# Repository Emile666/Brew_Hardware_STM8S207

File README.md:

# Brew Automation Hardware with a STM8S207
This PCB is an evolution of what originally was an Arduino with some added hardware. The current PCB features an STM8S207R8, which comes in a 64 pins LQPF package. It has a maximum of 52 GPIO pins, contains 64K Flash, 1536 bytes EEPROM and 6 KB of RAM. Previous PCB versions were made with Eagle, starting with V4.12, KiCad is used.

<br>
*PCB Layout*

# Features
The current PCB and firmware have the following features:
- Reading of **6 x temperature sensors**: two in the HLT (one I2C LM92, one One-Wire DS18B20), one in the MLT (I2C), one in the boil-kettle (One-Wire), one at the output of the counterflow-chiller (One-Wire) and one at the MLT return-manifold (One-Wire).
- Reading of **one hardware temperature** by a LM35 temperature sensor: this is used to protect the Solid State Relays (SSR) from overheating. The LM35 is typically mounted to a heatsink of one of the SSRs that switch a heating-element.
- Reading a maximum of **4 x FS300A flowsensors**: between HLT and MLT, between MLT and boil-kettle, one at the output of the counterflow-chiller and one at the entry of the MLT return-manifold.
- Control of **8 x solenoid ball-valves** at 24 V DC.
- **2 x PWM signals (25 kHz, 28 V DC)** for the modulating gasburners (HLT and boil-kettle burners).
- Control of **4 x SSR outputs at 230 V AC**: the pump, a second pump (for the HLT counterflow-chiller), 230 V enable for the HLT gasburner and 230 V enable for the boil-kettle gasburner.
- Control of **6 x SSR outputs at 230 V AC** for the three phase heating-elements in the HLT and the boil-kettle. With this, heating of the HLT is possible with a gas-burner, with 1, 2 or 3 heating-elements of with any combination of these.
- **Synced SSR outputs** for HLT and boil-kettle, so that you only need **one three-phase connection**. The boil-kettle outputs have priority over the HLT outputs, meaning that if (on any phase of 230 V) both HLT and boil-kettle are heating, only the boil-kettle is activated.
  It is also possible to use just one (or two) of the three-phases, depending on the number of heating-elements inside the HLT and/or boil-kettle. The firmware is capable of addressing one, two or three heating-elements per kettle.
- **Ethernet and USB connection** to PC: USB-connection is used for debugging, main connection between PC-program and the firmware is Ethernet.
- **Frontpanel LEDs (24 in total)** that show the status of all actuators. They are controlled by a MAX7219 LED Display Driver, located on a separate PCB, the frontpanel PCB.

# Schematics (.pdf)
[Brew Hardware schematics](./brew_HW_stm8s207_r430.pdf)<br>
*Brew Hardware Schematics*

# Interactive Bill-of-Materials (BOM)
[Brew Hardware BOM](http://htmlpreview.github.io/?https://github.com/Emile666/Brew_Hardware_STM8S207/blob/main/bom/ibom.html)<br>
*Brew Hardware BOM*

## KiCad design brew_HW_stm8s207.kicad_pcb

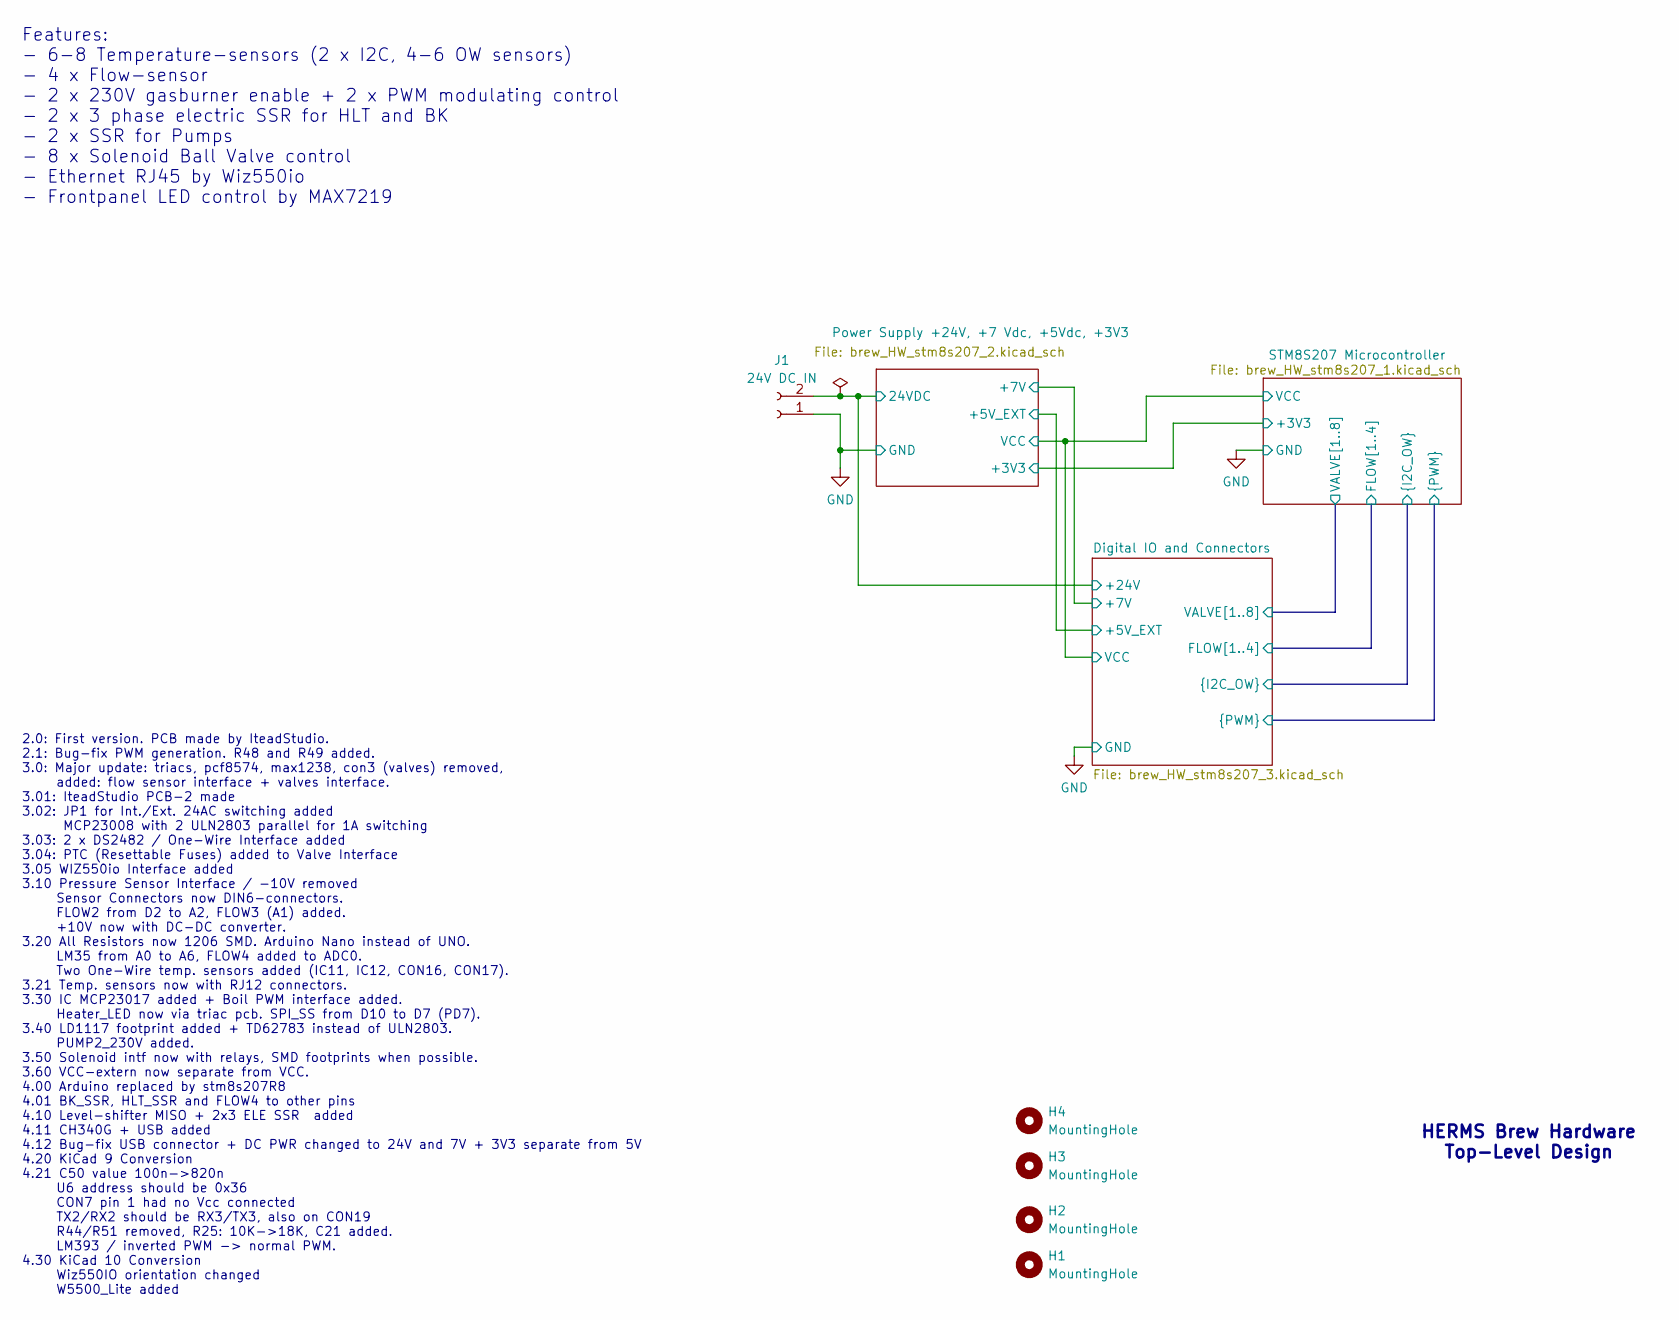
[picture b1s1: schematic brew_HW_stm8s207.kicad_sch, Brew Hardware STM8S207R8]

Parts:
H1, H2, H3, H4: MountingHole; MountingHole_3.2mm_M3
J1: 24V DC IN; AK500_2

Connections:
/Digital IO and Connectors/+24V: J1.2; also elsewhere on the board
GND: J1.1; also elsewhere on the board

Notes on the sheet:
Features: - 6-8 Temperature-sensors (2 x I2C, 4-6 OW sensors) - 4 x Flow-sensor - 2 x 230V gasburner enable + 2 x PWM modulating control - 2 x 3 phase electric SSR for HLT and BK - 2 x SSR for Pumps - 8 x Solenoid Ball Valve control - Ethernet RJ45 by Wiz550io - Frontpanel LED control by MAX7219
2.0: First version. PCB made by IteadStudio. 2.1: Bug-fix PWM generation. R48 and R49 added. 3.0: Major update: triacs, pcf8574, max1238, con3 (valves) removed, added: flow sensor interface + valves interface. 3.01: IteadStudio PCB-2 made 3.02: JP1 for Int./Ext. 24AC switching added MCP23008 with 2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
HERMS Brew Hardware Top-Level Design

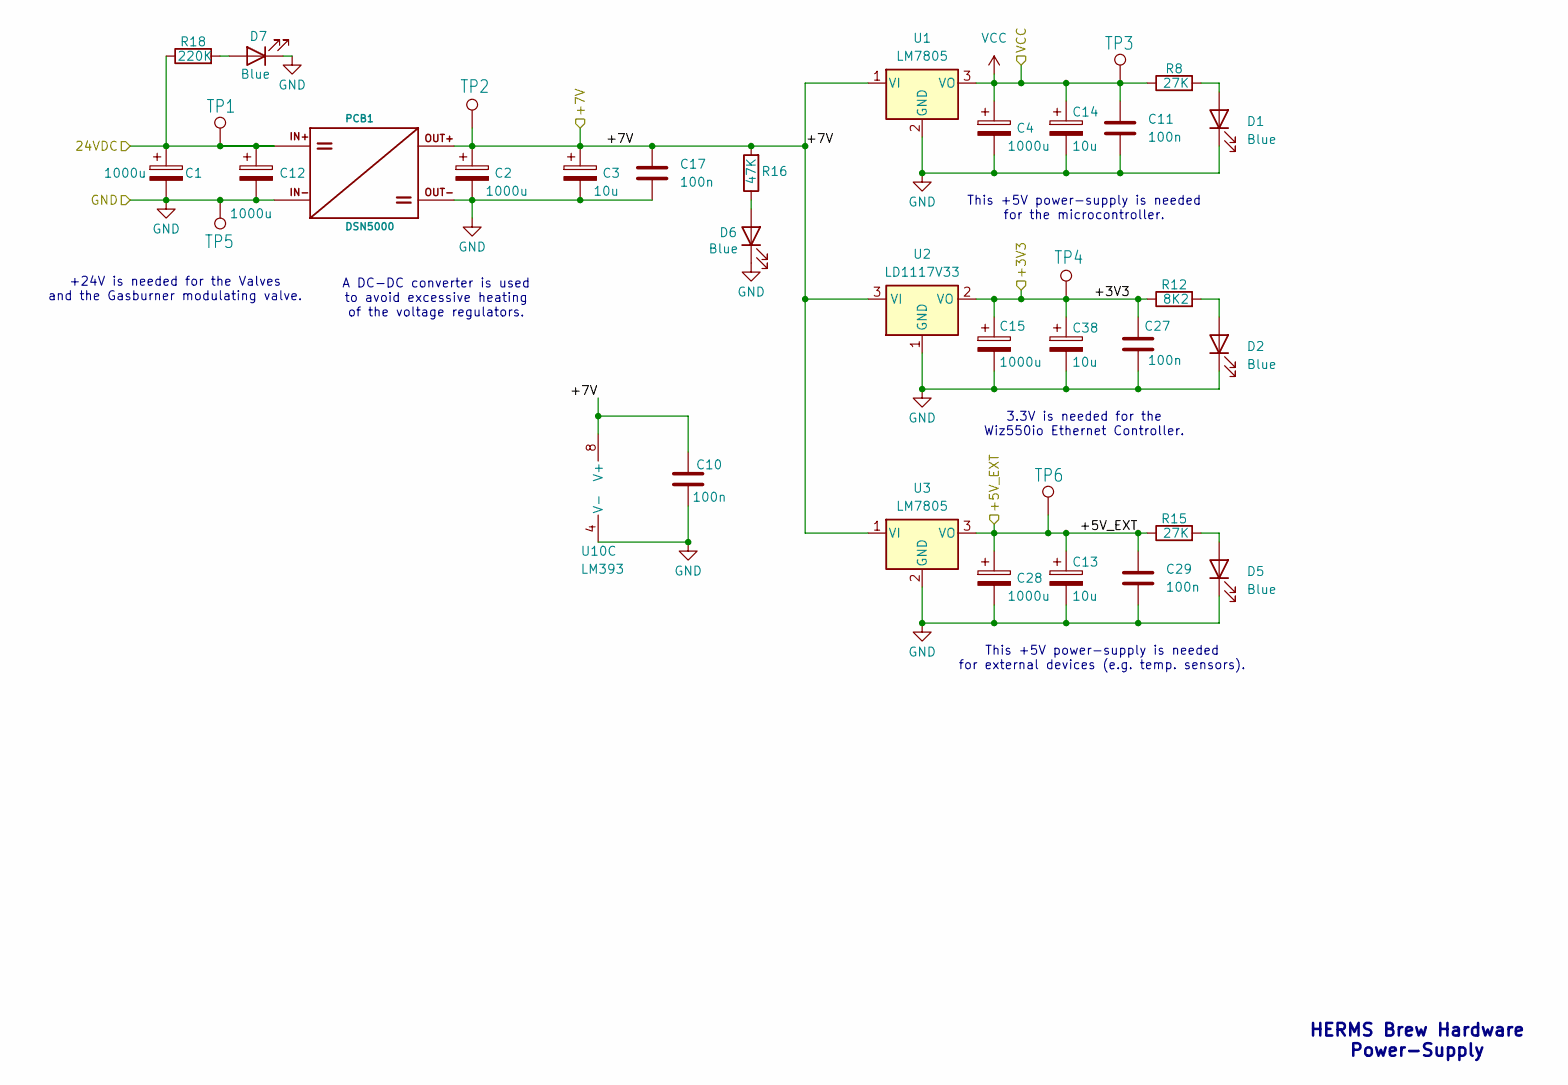
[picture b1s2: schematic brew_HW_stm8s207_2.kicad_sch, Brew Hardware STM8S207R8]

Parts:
C1, C2, C4, C12, C15, C28: 1000u; CP_Radial_D12.5mm_P5.00mm
C3, C13, C14, C38: 10u; CP_Radial_D5.0mm_P2.00mm
C10, C11, C17, C27, C29: 100n; C_1206_3216Metric
D1, D2, D5, D6, D7: Blue; LED_1206_3216Metric
PCB1: DSN5000; DSN5000_DCDC_CONVERTER
R8, R15: 27K; R_1206_3216Metric
R12: 8K2; R_1206_3216Metric
R16: 47K; R_1206_3216Metric
R18: 220K; R_1206_3216Metric
TP1: +24V; TestPoint_Loop_D2.54mm_Drill1.5mm_Beaded
TP2: +7V; TestPoint_Loop_D2.54mm_Drill1.5mm_Beaded
TP3: VCC; TestPoint_Loop_D2.54mm_Drill1.5mm_Beaded
TP4: +3V3; TestPoint_Loop_D2.54mm_Drill1.5mm_Beaded
TP5: GND; TestPoint_Loop_D2.54mm_Drill1.5mm_Beaded
TP6: +5VE; TestPoint_Loop_D2.54mm_Drill1.5mm_Beaded
U1, U3: LM7805; TO-220-3_Vertical
U2: LD1117V33; TO-220-3_Vertical
U10: LM393; DIP-8_W7.62mm

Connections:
/Digital IO and Connectors/+5V_EXT: C13.1, C28.1, C29.1, R15.1, TP6.1 (1_1), U3.3 (VO); also elsewhere on the board
/Digital IO and Connectors/+7V: C2.1, C3.1, C10.1, C17.1, PCB1.P$3, R16.2, TP2.1 (1_1), U1.1 (VI), U2.3 (VI), U3.1 (VI), U10.8 (V+); also elsewhere on the board
/Digital IO and Connectors/+24V: C1.1, C12.1, PCB1.PX$1 (IN+), R18.1, TP1.1 (1_1); also elsewhere on the board
/Power Supply +24V, +7 Vdc, +5Vdc, +3V3/+3V3: C15.1, C27.1, C38.1, R12.1, TP4.1 (1_1), U2.2 (VO); also elsewhere on the board
GND: C1.2, C2.2, C3.2, C4.2, C10.2, C11.2, C12.2, C13.2, C14.2, C15.2, C17.2, C27.2, C28.2, C29.2, C38.2, D1.1 (K), D2.1 (K), D5.1 (K), D6.1 (K), D7.1 (K), PCB1.P$2, PCB1.P$4, TP5.1 (1_1), U1.2 (GND), U2.1 (GND), U3.2 (GND), U10.4 (V-); also elsewhere on the board
unnamed: D1.2 (A), R8.2
unnamed: D2.2 (A), R12.2
unnamed: D5.2 (A), R15.2
unnamed: D6.2 (A), R16.1
unnamed: D7.2 (A), R18.2
VCC: C4.1, C11.1, C14.1, R8.1, TP3.1 (1_1), U1.3 (VO); also elsewhere on the board

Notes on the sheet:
This +5V power-supply is needed for external devices (e.g. temp. sensors).
+24V is needed for the Valves and the Gasburner modulating valve.
HERMS Brew Hardware Power-Supply
This +5V power-supply is needed for the microcontroller.
A DC-DC converter is used to avoid excessive heating of the voltage regulators.
3.3V is needed for the Wiz550io Ethernet Controller.

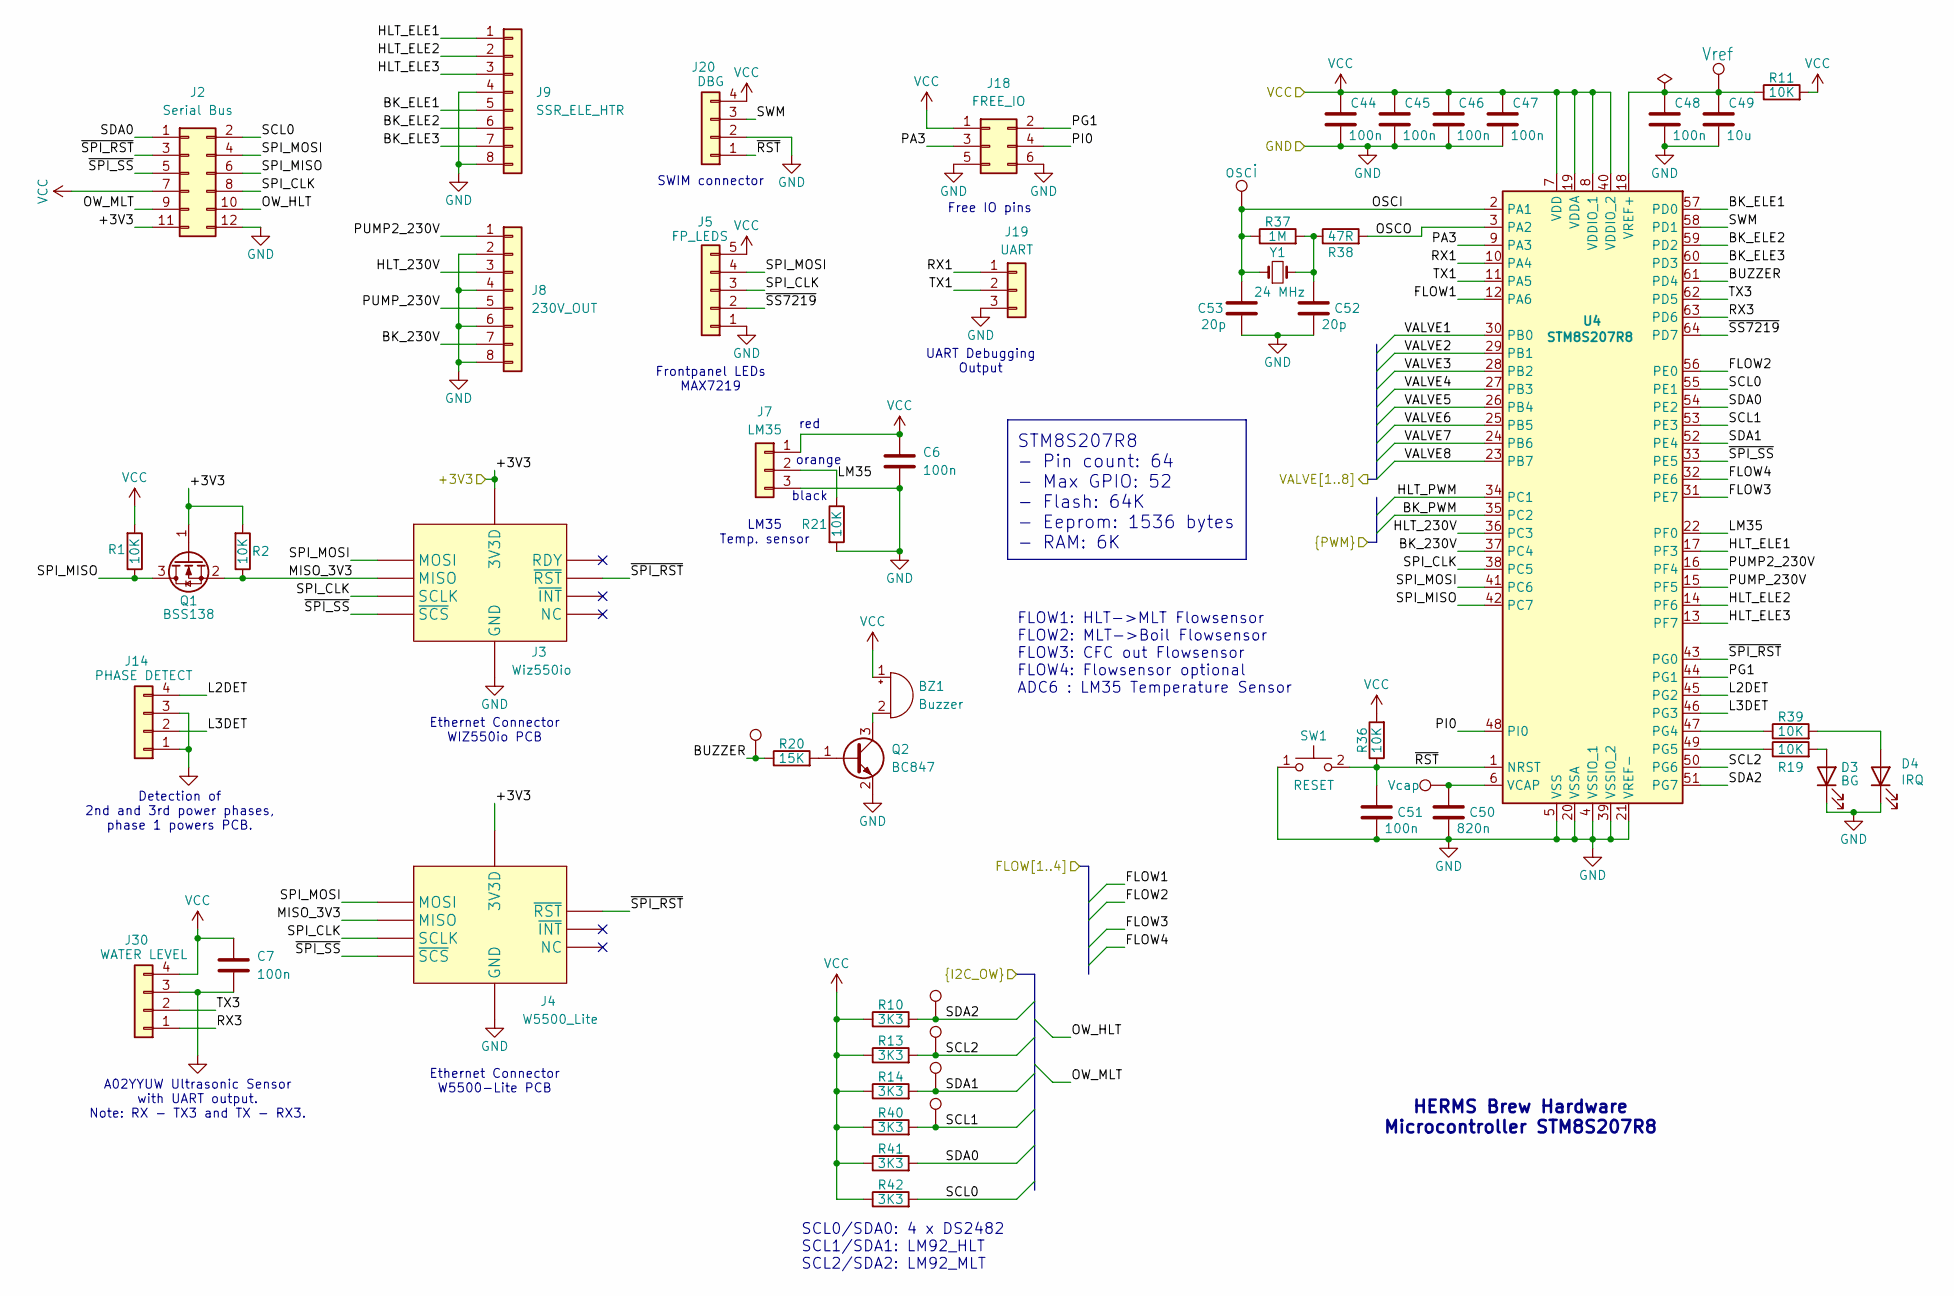
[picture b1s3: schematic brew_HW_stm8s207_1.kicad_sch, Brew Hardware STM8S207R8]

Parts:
BZ1: Buzzer; Buzzer_12x9.5RM7.6
C6, C7, C44, C45, C46, C47, C48, C51: 100n; C_1206_3216Metric
C49: 10u; CP_Radial_D5.0mm_P2.00mm
C50: 820n; C_1206_3216Metric
C52, C53: 20p; C_1206_3216Metric
D3: BG; LED_1206_3216Metric
D4: IRQ; LED_1206_3216Metric
J2: Serial Bus; PinSocket_2x06_P2.54mm_Vertical
J3: Wiz550io; WIZ550IO
J4: W5500_Lite; W55000_Lite
J5: FP_LEDS; PinSocket_1x05_P2.54mm_Vertical
J7: LM35; PinSocket_1x03_P2.54mm_Vertical
J8: 230V_OUT; PinHeader_1x08_P2.54mm_Vertical
J9: SSR_ELE_HTR; PinHeader_1x08_P2.54mm_Vertical
J14: PHASE DETECT; PinSocket_1x04_P2.54mm_Vertical
J18: FREE_IO; PinSocket_2x03_P2.54mm_Vertical
J19: UART; PinSocket_1x03_P2.54mm_Vertical
J20: DBG; PinSocket_1x04_P2.54mm_Vertical
J30: WATER LEVEL; PinSocket_1x04_P2.54mm_Vertical
Q1: BSS138; SOT-23
Q2: BC847; SOT-23
R1, R2, R11, R19, R21, R36, R39: 10K; R_1206_3216Metric
R10, R13, R14, R40, R41, R42: 3K3; R_1206_3216Metric
R20: 15K; R_1206_3216Metric
R37: 1M; R_1206_3216Metric
R38: 47R; R_1206_3216Metric
SW1: RESET; SW_Tactile_Straight_KSA0Axx1LFTR
TP7: Vref; TestPoint_Pad_D1.0mm
TP8: Vcap; TestPoint_Pad_D1.0mm
TP9: sda2; TestPoint_Pad_D1.0mm
TP10: scl2; TestPoint_Pad_D1.0mm
TP11: sda1; TestPoint_Pad_D1.0mm
TP12: scl1; TestPoint_Pad_D1.0mm
TP13: bz; TestPoint_Pad_D1.0mm
TP14: osci; TestPoint_Pad_D1.0mm
U4: STM8S207R8; LQFP-64_10x10mm_P0.5mm
Y1: 24 MHz; Crystal_HC49-4H_Vertical

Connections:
/Digital IO and Connectors/BK_PWM: U4.35 (PC2); also elsewhere on the board
/Digital IO and Connectors/FLOW1: U4.12 (PA6); also elsewhere on the board
/Digital IO and Connectors/FLOW2: U4.56 (PE0); also elsewhere on the board
/Digital IO and Connectors/FLOW3: U4.31 (PE7); also elsewhere on the board
/Digital IO and Connectors/FLOW4: U4.32 (PE6); also elsewhere on the board
/Digital IO and Connectors/HLT_PWM: U4.34 (PC1); also elsewhere on the board
/Digital IO and Connectors/OW_HLT: J2.10; also elsewhere on the board
/Digital IO and Connectors/OW_MLT: J2.9; also elsewhere on the board
/Digital IO and Connectors/SCL0: J2.2, R42.2, U4.55 (PE1); also elsewhere on the board
/Digital IO and Connectors/SCL1: R40.2, TP12.1 (1_1), U4.53 (PE3); also elsewhere on the board
/Digital IO and Connectors/SCL2: R13.2, TP10.1 (1_1), U4.50 (PG6); also elsewhere on the board
/Digital IO and Connectors/SDA0: J2.1, R41.2, U4.54 (PE2); also elsewhere on the board
/Digital IO and Connectors/SDA1: R14.2, TP11.1 (1_1), U4.52 (PE4); also elsewhere on the board
/Digital IO and Connectors/SDA2: R10.2, TP9.1 (1_1), U4.51 (PG7); also elsewhere on the board
/Digital IO and Connectors/VALVE1: U4.30 (PB0); also elsewhere on the board
/Digital IO and Connectors/VALVE2: U4.29 (PB1); also elsewhere on the board
/Digital IO and Connectors/VALVE3: U4.28 (PB2); also elsewhere on the board
/Digital IO and Connectors/VALVE4: U4.27 (PB3); also elsewhere on the board
/Digital IO and Connectors/VALVE5: U4.26 (PB4); also elsewhere on the board
/Digital IO and Connectors/VALVE6: U4.25 (PB5); also elsewhere on the board
/Digital IO and Connectors/VALVE7: U4.24 (PB6); also elsewhere on the board
/Digital IO and Connectors/VALVE8: U4.23 (PB7); also elsewhere on the board
/Power Supply +24V, +7 Vdc, +5Vdc, +3V3/+3V3: J2.11, J3.6 (3V3D), J4.6 (3V3D), Q1.1 (G), R2.2; also elsewhere on the board
/STM8S207 Microcontroller/BK_230V: J8.7, U4.37 (PC4)
/STM8S207 Microcontroller/BK_ELE1: J9.5, U4.57 (PD0)
/STM8S207 Microcontroller/BK_ELE2: J9.6, U4.59 (PD2)
/STM8S207 Microcontroller/BK_ELE3: J9.7, U4.60 (PD3)
/STM8S207 Microcontroller/BUZZER: R20.1, TP13.1 (1_1), U4.61 (PD4)
/STM8S207 Microcontroller/HLT_230V: J8.3, U4.36 (PC3)
/STM8S207 Microcontroller/HLT_ELE1: J9.1, U4.17 (PF3)
/STM8S207 Microcontroller/HLT_ELE2: J9.2, U4.14 (PF6)
/STM8S207 Microcontroller/HLT_ELE3: J9.3, U4.13 (PF7)
/STM8S207 Microcontroller/L2DET: J14.4, U4.45 (PG2)
/STM8S207 Microcontroller/L3DET: J14.2, U4.46 (PG3)
/STM8S207 Microcontroller/LM35: J7.2, R21.1, U4.22 (PF0)
/STM8S207 Microcontroller/MISO_3V3: J3.3 (MISO), J4.3 (MISO), Q1.2 (S), R2.1
/STM8S207 Microcontroller/OSCI: C53.1, R37.1, TP14.1 (1_1), U4.2 (PA1), Y1.1
/STM8S207 Microcontroller/OSCO: R38.2, U4.3 (PA2)
/STM8S207 Microcontroller/PA3: J18.3, U4.9 (PA3)
/STM8S207 Microcontroller/PG1: J18.2, U4.44 (PG1)
/STM8S207 Microcontroller/PI0: J18.4, U4.48 (PI0)
/STM8S207 Microcontroller/PUMP2_230V: J8.1, U4.16 (PF4)
/STM8S207 Microcontroller/PUMP_230V: J8.5, U4.15 (PF5)
/STM8S207 Microcontroller/RX1: J19.1, U4.10 (PA4)
/STM8S207 Microcontroller/RX3: J30.1, U4.63 (PD6)
/STM8S207 Microcontroller/SPI_CLK: J2.8, J3.4 (SCLK), J4.4 (SCLK), J5.3, U4.38 (PC5)
/STM8S207 Microcontroller/SPI_MISO: J2.6, Q1.3 (D), R1.1, U4.42 (PC7)
/STM8S207 Microcontroller/SPI_MOSI: J2.4, J3.2 (MOSI), J4.2 (MOSI), J5.4, U4.41 (PC6)
/STM8S207 Microcontroller/SWM: J20.3, U4.58 (PD1)
/STM8S207 Microcontroller/TX1: J19.2, U4.11 (PA5)
/STM8S207 Microcontroller/TX3: J30.2, U4.62 (PD5)
/STM8S207 Microcontroller/~RST: C51.1, J20.1, R36.1, SW1.2, U4.1 (NRST)
/STM8S207 Microcontroller/~SPI_RST: J2.3, J3.9 (~RST), J4.9 (~RST), U4.43 (PG0)
/STM8S207 Microcontroller/~SPI_SS: J2.5, J3.5 (~SCS), J4.5 (~SCS), U4.33 (PE5)
/STM8S207 Microcontroller/~SS7219: J5.2, U4.64 (PD7)
GND: C6.2, C7.2, C44.2, C45.2, C46.2, C47.2, C48.2, C49.2, C50.2, C51.2, C52.2, C53.2, D3.1 (K), D4.1 (K), J2.12, J3.1 (GND), J4.1 (GND), J5.1, J7.3, J8.2, J8.4, J8.6, J8.8, J9.4, J9.8, J14.1, J14.3, J18.5, J18.6, J19.3, J20.2, J30.3, Q2.2 (E), R21.2, SW1.1, U4.4 (VSSIO_1), U4.5 (VSS), U4.20 (VSSA), U4.21 (VREF-), U4.39 (VSSIO_2); also elsewhere on the board
unnamed: BZ1.2 (-), Q2.3 (C)
unnamed: C52.1, R37.2, R38.1, Y1.2
unnamed: D3.2 (A), R19.2
unnamed: D4.2 (A), R39.2
unnamed: Q2.1 (B), R20.2
unnamed: R39.1, U4.47 (PG4)
unnamed: R19.1, U4.49 (PG5)
unnamed: C50.1, TP8.1 (1_1), U4.6 (VCAP)
unnamed: C48.1, C49.1, R11.1, TP7.1 (1_1), U4.18 (VREF+)
VCC: BZ1.1 (+), C6.1, C7.1, C44.1, C45.1, C46.1, C47.1, J2.7, J5.5, J7.1, J18.1, J20.4, J30.4, R1.2, R10.1, R11.2, R13.1, R14.1, R36.2, R40.1, R41.1, R42.1, U4.7 (VDD), U4.8 (VDDIO_1), U4.19 (VDDA), U4.40 (VDDIO_2); also elsewhere on the board

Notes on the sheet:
SWIM connector
Ethernet Connector WIZ550io PCB
SCL0/SDA0: 4 x DS2482 SCL1/SDA1: LM92_HLT SCL2/SDA2: LM92_MLT
black
FLOW1: HLT->MLT Flowsensor FLOW2: MLT->Boil Flowsensor FLOW3: CFC out Flowsensor FLOW4: Flowsensor optional ADC6 : LM35 Temperature Sensor
LM35 Temp. sensor
Frontpanel LEDs MAX7219
Ethernet Connector W5500-Lite PCB
orange
HERMS Brew Hardware Microcontroller STM8S207R8
STM8S207R8 - Pin count: 64 - Max GPIO: 52 - Flash: 64K - Eeprom: 1536 bytes - RAM: 6K
UART Debugging Output
A02YYUW Ultrasonic Sensor with UART output. Note: RX - TX3 and TX - RX3.
Detection of 2nd and 3rd power phases, phase 1 powers PCB.
Free IO pins
red

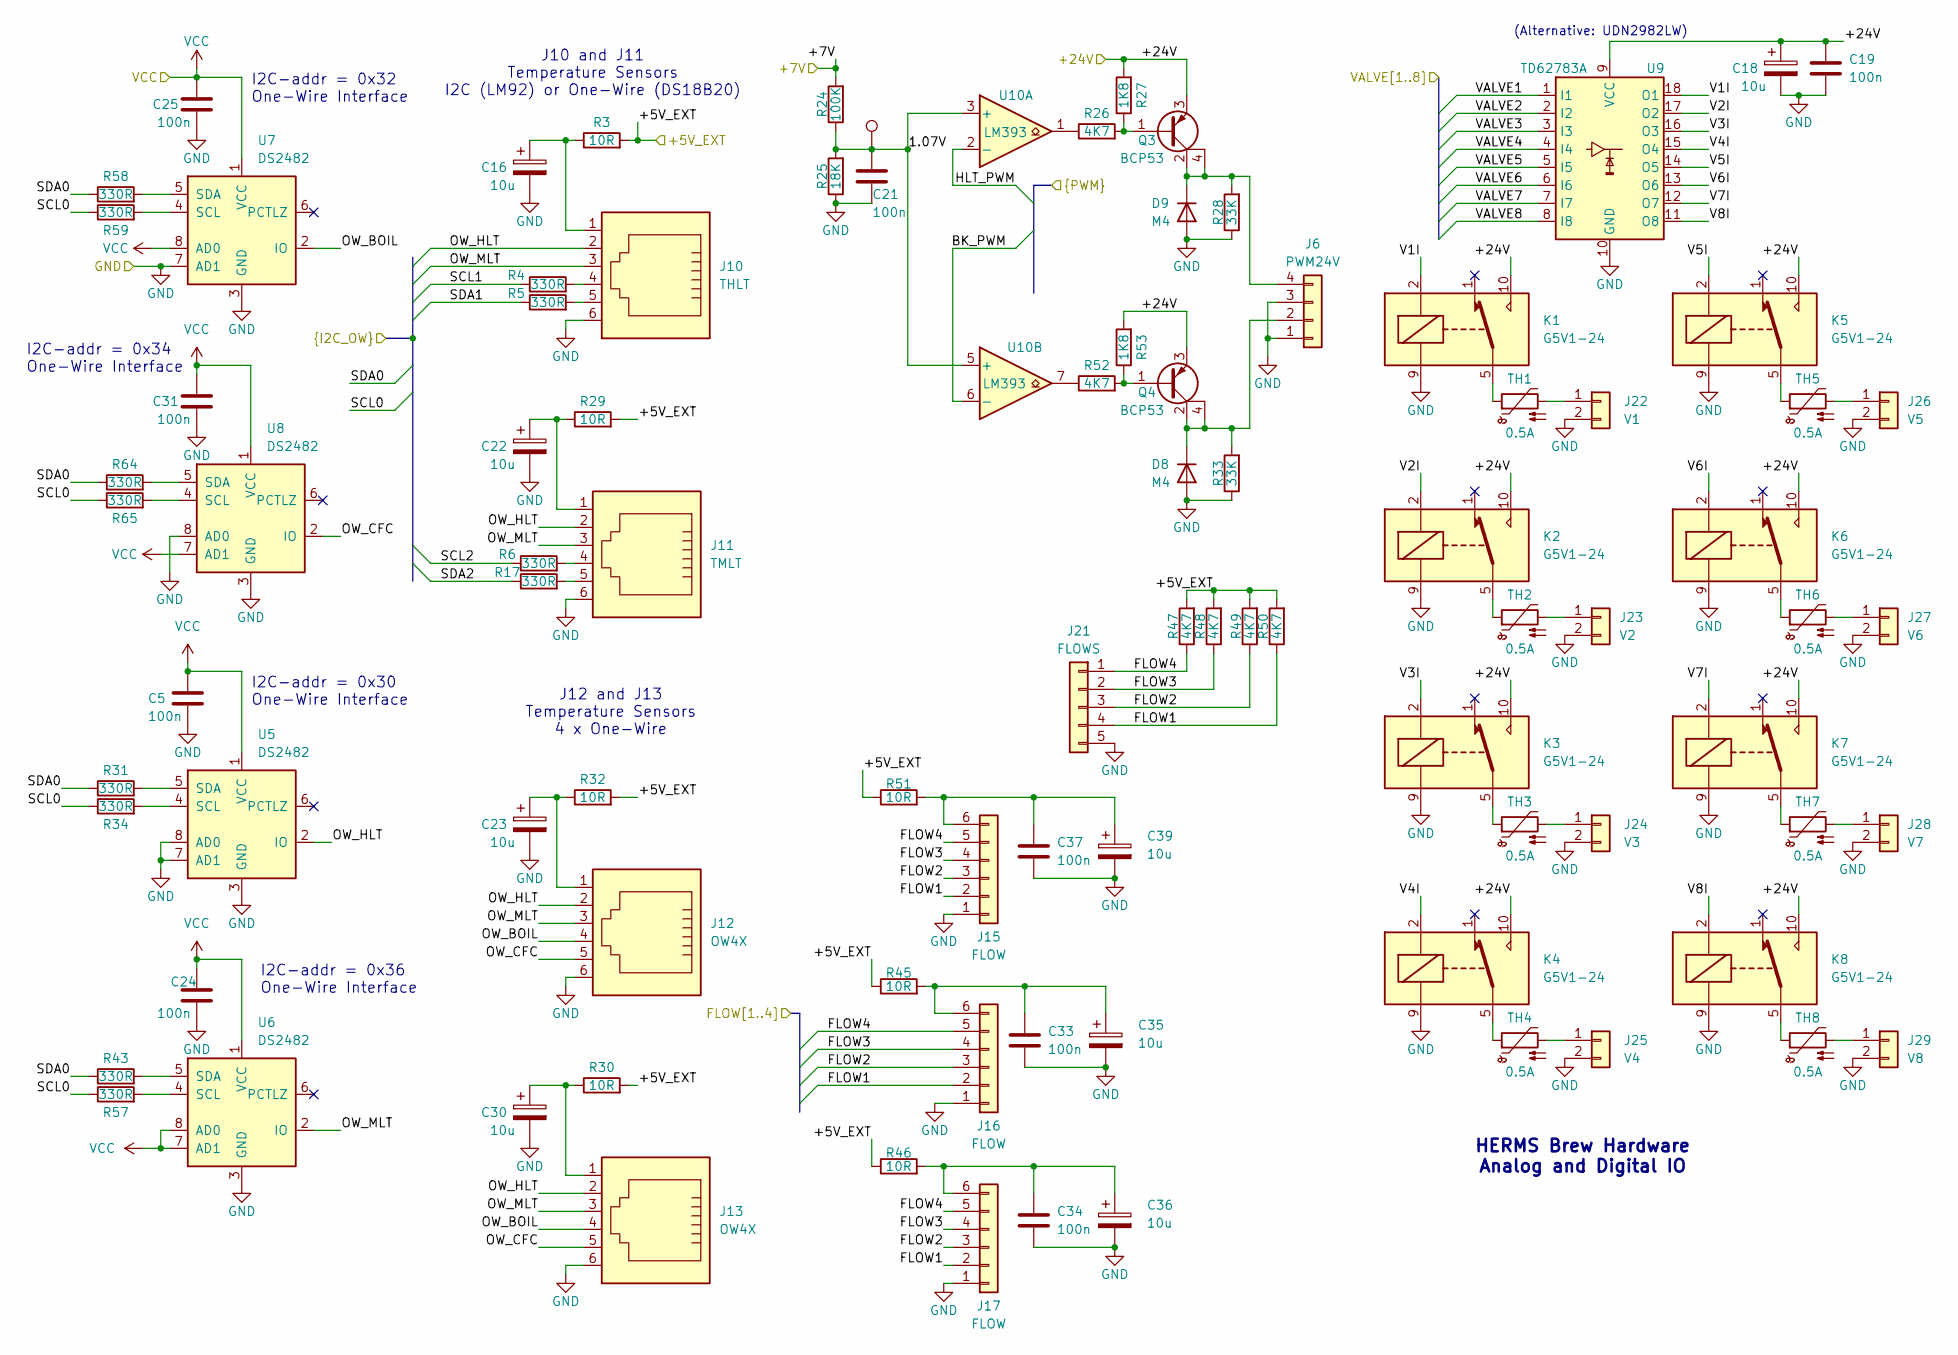
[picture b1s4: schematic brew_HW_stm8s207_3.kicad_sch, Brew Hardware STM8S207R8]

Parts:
C5, C19, C21, C24, C25, C31, C33, C34, C37: 100n; C_1206_3216Metric
C16, C18, C22, C23, C30, C35, C36, C39: 10u; CP_Radial_D5.0mm_P2.00mm
D8, D9: M4; D_SMA_Handsoldering
J6: PWM24V; PinSocket_1x04_P2.54mm_Vertical
J10: THLT; RJ12_Amphenol_54601-x06_Horizontal
J11: TMLT; RJ12_Amphenol_54601-x06_Horizontal
J12, J13: OW4X; RJ12_Amphenol_54601-x06_Horizontal
J15, J16, J17: FLOW; PS2-MINI-DIN6
J21: FLOWS; PinSocket_1x05_P2.54mm_Vertical
J22: V1; PinSocket_1x02_P2.54mm_Vertical
J23: V2; PinSocket_1x02_P2.54mm_Vertical
J24: V3; PinSocket_1x02_P2.54mm_Vertical
J25: V4; PinSocket_1x02_P2.54mm_Vertical
J26: V5; PinSocket_1x02_P2.54mm_Vertical
J27: V6; PinSocket_1x02_P2.54mm_Vertical
J28: V7; PinSocket_1x02_P2.54mm_Vertical
J29: V8; PinSocket_1x02_P2.54mm_Vertical
K1, K2, K3, K4, K5, K6, K7, K8: G5V1-24; Relay_SPDT_Omron_G5V-1
Q3, Q4: BCP53; SOT-223
R3, R29, R30, R32, R45, R46, R51: 10R; R_1206_3216Metric
R4, R5, R6, R17, R31, R34, R43, R57, R58, R59, R64, R65: 330R; R_1206_3216Metric
R24: 100K; R_1206_3216Metric
R25: 18K; R_1206_3216Metric
R26, R47, R48, R49, R50, R52: 4K7; R_1206_3216Metric
R27, R53: 1K8; R_1206_3216Metric
R28, R33: 33K; R_1206_3216Metric
TH1, TH2, TH3, TH4, TH5, TH6, TH7, TH8: 0.5A; R_Box_L8.4mm_W2.5mm_P5.08mm
TP15: 1V07; TestPoint_Pad_D1.0mm
U5, U6, U7, U8: DS2482; SOIC-8_3.9x4.9mm_P1.27mm
U9: TD62783A; SOIC-18W_7.5x11.6mm_P1.27mm
U10: LM393; DIP-8_W7.62mm

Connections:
/Digital IO and Connectors/1.07V: C21.1, R24.1, R25.2, TP15.1 (1_1), U10.3 (+), U10.5 (+)
/Digital IO and Connectors/+5V_EXT: R3.2, R29.2, R30.2, R32.2, R45.1, R46.1, R47.2, R48.2, R49.2, R50.2, R51.1; also elsewhere on the board
/Digital IO and Connectors/+7V: R24.2; also elsewhere on the board
/Digital IO and Connectors/+24V: C18.1, C19.1, K1.10, K2.10, K3.10, K4.10, K5.10, K6.10, K7.10, K8.10, Q3.3 (E), Q4.3 (E), R27.2, R53.2, U9.9 (VCC); also elsewhere on the board
/Digital IO and Connectors/BK_PWM: U10.6 (-); also elsewhere on the board
/Digital IO and Connectors/FLOW1: J15.2, J16.2, J17.2, J21.4, R50.1; also elsewhere on the board
/Digital IO and Connectors/FLOW2: J15.3, J16.3, J17.3, J21.3, R49.1; also elsewhere on the board
/Digital IO and Connectors/FLOW3: J15.4, J16.4, J17.4, J21.2, R48.1; also elsewhere on the board
/Digital IO and Connectors/FLOW4: J15.5, J16.5, J17.5, J21.1, R47.1; also elsewhere on the board
/Digital IO and Connectors/HLT_PWM: U10.2 (-); also elsewhere on the board
/Digital IO and Connectors/OW_BOIL: J12.4, J13.4, U7.2 (IO)
/Digital IO and Connectors/OW_CFC: J12.5, J13.5, U8.2 (IO)
/Digital IO and Connectors/OW_HLT: J10.2, J11.2, J12.2, J13.2, U5.2 (IO); also elsewhere on the board
/Digital IO and Connectors/OW_MLT: J10.3, J11.3, J12.3, J13.3, U6.2 (IO); also elsewhere on the board
/Digital IO and Connectors/SCL0: R34.1, R57.1, R59.1, R65.1; also elsewhere on the board
/Digital IO and Connectors/SCL1: R4.1; also elsewhere on the board
/Digital IO and Connectors/SCL2: R6.1; also elsewhere on the board
/Digital IO and Connectors/SDA0: R31.1, R43.1, R58.1, R64.1; also elsewhere on the board
/Digital IO and Connectors/SDA1: R5.1; also elsewhere on the board
/Digital IO and Connectors/SDA2: R17.1; also elsewhere on the board
/Digital IO and Connectors/V1I: K1.2, U9.18 (O1)
/Digital IO and Connectors/V2I: K2.2, U9.17 (O2)
/Digital IO and Connectors/V3I: K3.2, U9.16 (O3)
/Digital IO and Connectors/V4I: K4.2, U9.15 (O4)
/Digital IO and Connectors/V5I: K5.2, U9.14 (O5)
/Digital IO and Connectors/V6I: K6.2, U9.13 (O6)
/Digital IO and Connectors/V7I: K7.2, U9.12 (O7)
/Digital IO and Connectors/V8I: K8.2, U9.11 (O8)
/Digital IO and Connectors/VALVE1: U9.1 (I1); also elsewhere on the board
/Digital IO and Connectors/VALVE2: U9.2 (I2); also elsewhere on the board
/Digital IO and Connectors/VALVE3: U9.3 (I3); also elsewhere on the board
/Digital IO and Connectors/VALVE4: U9.4 (I4); also elsewhere on the board
/Digital IO and Connectors/VALVE5: U9.5 (I5); also elsewhere on the board
/Digital IO and Connectors/VALVE6: U9.6 (I6); also elsewhere on the board
/Digital IO and Connectors/VALVE7: U9.7 (I7); also elsewhere on the board
/Digital IO and Connectors/VALVE8: U9.8 (I8); also elsewhere on the board
GND: C5.2, C16.2, C18.2, C19.2, C21.2, C22.2, C23.2, C24.2, C25.2, C30.2, C31.2, C33.2, C34.2, C35.2, C36.2, C37.2, C39.2, D8.2 (A), D9.2 (A), J6.1, J6.3, J10.6, J11.6, J12.6, J13.6, J15.1, J16.1, J17.1, J21.5, J22.2, J23.2, J24.2, J25.2, J26.2, J27.2, J28.2, J29.2, K1.9, K2.9, K3.9, K4.9, K5.9, K6.9, K7.9, K8.9, R25.1, R28.1, R33.1, U5.3 (GND), U5.7 (AD1), U5.8 (AD0), U6.3 (GND), U7.3 (GND), U7.7 (AD1), U8.3 (GND), U8.8 (AD0), U9.10 (GND); also elsewhere on the board
unnamed: C16.1, J10.1, R3.1
unnamed: C22.1, J11.1, R29.1
unnamed: C23.1, J12.1, R32.1
unnamed: C30.1, J13.1, R30.1
unnamed: D8.1 (K), J6.2, Q4.2 (C), Q4.4 (C), R33.2
unnamed: D9.1 (K), J6.4, Q3.2 (C), Q3.4 (C), R28.2
unnamed: J10.4, R4.2
unnamed: J10.5, R5.2
unnamed: J11.4, R6.2
unnamed: J11.5, R17.2
unnamed: C37.1, C39.1, J15.6, R51.2
unnamed: C33.1, C35.1, J16.6, R45.2
unnamed: C34.1, C36.1, J17.6, R46.2
unnamed: J22.1, TH1.2
unnamed: J23.1, TH2.2
unnamed: J24.1, TH3.2
unnamed: J25.1, TH4.2
unnamed: J26.1, TH5.2
unnamed: J27.1, TH6.2
unnamed: J28.1, TH7.2
unnamed: J29.1, TH8.2
unnamed: K1.5, K1.6, TH1.1
unnamed: K2.5, K2.6, TH2.1
unnamed: K3.5, K3.6, TH3.1
unnamed: K4.5, K4.6, TH4.1
unnamed: K5.5, K5.6, TH5.1
unnamed: K6.5, K6.6, TH6.1
unnamed: K7.5, K7.6, TH7.1
unnamed: K8.5, K8.6, TH8.1
unnamed: Q3.1 (B), R26.2, R27.1
unnamed: Q4.1 (B), R52.2, R53.1
unnamed: R26.1, U10.1
unnamed: R52.1, U10.7
unnamed: R34.2, U5.4 (SCL)
unnamed: R31.2, U5.5 (SDA)
unnamed: R57.2, U6.4 (SCL)
unnamed: R43.2, U6.5 (SDA)
unnamed: R59.2, U7.4 (SCL)
unnamed: R58.2, U7.5 (SDA)
unnamed: R65.2, U8.4 (SCL)
unnamed: R64.2, U8.5 (SDA)
VCC: C5.1, C24.1, C25.1, C31.1, U5.1 (VCC), U6.1 (VCC), U6.7 (AD1), U6.8 (AD0), U7.1 (VCC), U7.8 (AD0), U8.1 (VCC), U8.7 (AD1); also elsewhere on the board

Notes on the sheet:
I2C-addr = 0x34 One-Wire Interface
(Alternative: UDN2982LW)
J12 and J13 Temperature Sensors 4 x One-Wire
I2C-addr = 0x30 One-Wire Interface
HERMS Brew Hardware Analog and Digital IO
I2C-addr = 0x32 One-Wire Interface
I2C-addr = 0x36 One-Wire Interface
J10 and J11 Temperature Sensors I2C (LM92) or One-Wire (DS18B20)

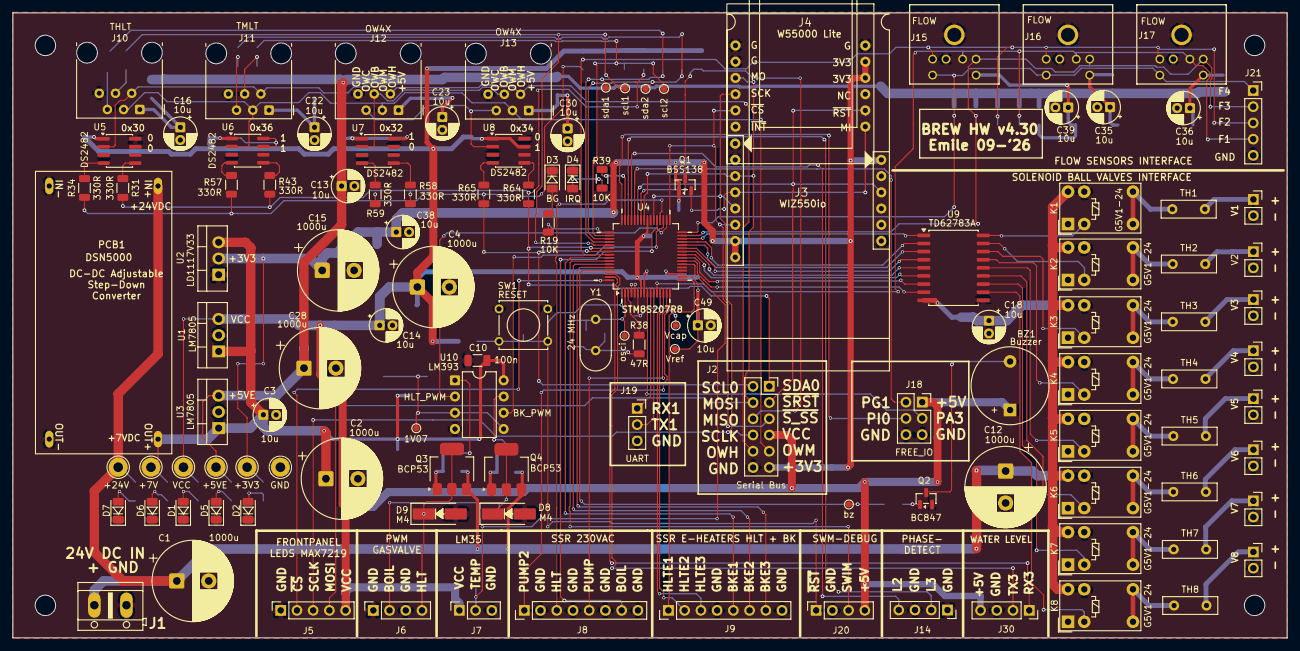
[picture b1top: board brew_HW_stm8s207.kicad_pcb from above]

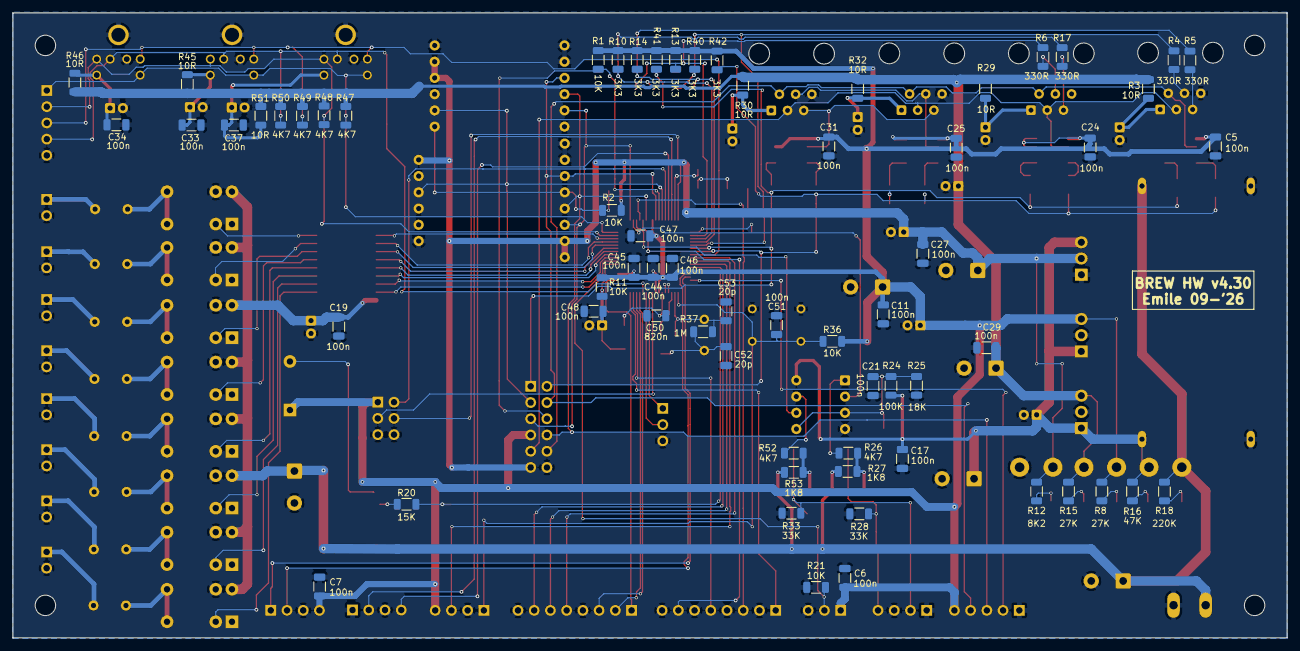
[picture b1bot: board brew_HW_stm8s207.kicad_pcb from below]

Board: 2 copper layers, 199.4 x 97.8 mm, 188 parts (65 on the bottom side), 126 nets.
